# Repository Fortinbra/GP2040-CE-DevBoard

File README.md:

# GP2040-CE-DevBoard
Development board for the GP2040-CE firmware

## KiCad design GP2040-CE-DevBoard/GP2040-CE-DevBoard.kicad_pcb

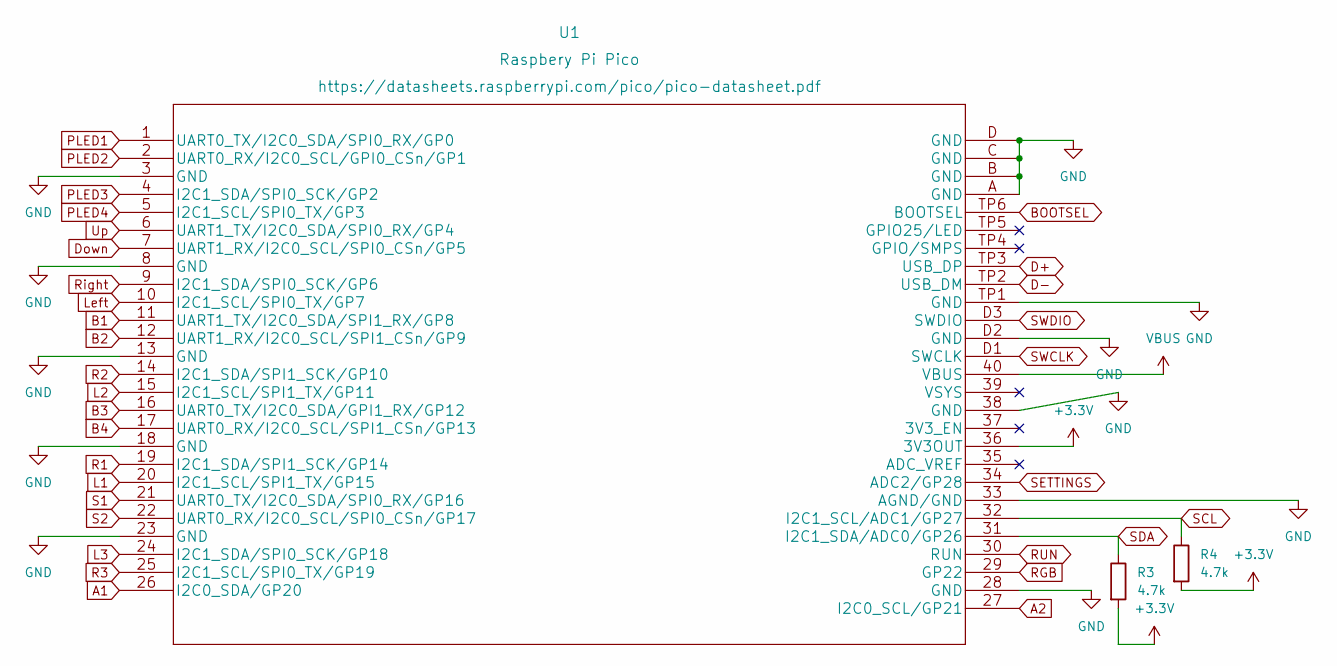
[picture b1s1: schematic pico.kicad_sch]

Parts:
R3, R4: 4.7k; C_0805_2012Metric_Pad1.18x1.45mm_HandSolder
U1: Raspbery Pi Pico; Pico

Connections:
+3V3: R3.2, R4.2, U1.36 (3V3OUT); also elsewhere on the board
A1: U1.26 (I2C0_SDA/GP20); also elsewhere on the board
A2: U1.27 (I2C0_SCL/GP21); also elsewhere on the board
B1: U1.11 (UART1_TX/I2C0_SDA/SPI1_RX/GP8); also elsewhere on the board
B2: U1.12 (UART1_RX/I2C0_SCL/SPI1_CSn/GP9); also elsewhere on the board
B3: U1.16 (UART0_TX/I2C0_SDA/GPI1_RX/GP12); also elsewhere on the board
B4: U1.17 (UART0_RX/I2C0_SCL/SPI1_CSn/GP13); also elsewhere on the board
BOOTSEL: U1.TP6 (BOOTSEL); also elsewhere on the board
D+: U1.TP3 (USB_DP); also elsewhere on the board
D-: U1.TP2 (USB_DM); also elsewhere on the board
Down: U1.7 (UART1_RX/I2C0_SCL/SPI0_CSn/GP5); also elsewhere on the board
GND: U1.3 (GND), U1.8 (GND), U1.13 (GND), U1.18 (GND), U1.23 (GND), U1.28 (GND), U1.33 (AGND/GND), U1.38 (GND), U1.A (GND), U1.B (GND), U1.C (GND), U1.D (GND), U1.D2 (GND), U1.TP1 (GND); also elsewhere on the board
L1: U1.20 (I2C1_SCL/SPI1_TX/GP15); also elsewhere on the board
L2: U1.15 (I2C1_SCL/SPI1_TX/GP11); also elsewhere on the board
L3: U1.24 (I2C1_SDA/SPI0_SCK/GP18); also elsewhere on the board
Left: U1.10 (I2C1_SCL/SPI0_TX/GP7); also elsewhere on the board
PLED1: U1.1 (UART0_TX/I2C0_SDA/SPI0_RX/GP0); also elsewhere on the board
PLED2: U1.2 (UART0_RX/I2C0_SCL/GPI0_CSn/GP1); also elsewhere on the board
PLED3: U1.4 (I2C1_SDA/SPI0_SCK/GP2); also elsewhere on the board
PLED4: U1.5 (I2C1_SCL/SPI0_TX/GP3); also elsewhere on the board
R1: U1.19 (I2C1_SDA/SPI1_SCK/GP14); also elsewhere on the board
R2: U1.14 (I2C1_SDA/SPI1_SCK/GP10); also elsewhere on the board
R3: U1.25 (I2C1_SCL/SPI0_TX/GP19); also elsewhere on the board
RGB: U1.29 (GP22); also elsewhere on the board
RUN: U1.30 (RUN); also elsewhere on the board
Right: U1.9 (I2C1_SDA/SPI0_SCK/GP6); also elsewhere on the board
S1: U1.21 (UART0_TX/I2C0_SDA/SPI0_RX/GP16); also elsewhere on the board
S2: U1.22 (UART0_RX/I2C0_SCL/SPI0_CSn/GP17); also elsewhere on the board
SCL: R4.1, U1.32 (I2C1_SCL/ADC1/GP27); also elsewhere on the board
SDA: R3.1, U1.31 (I2C1_SDA/ADC0/GP26); also elsewhere on the board
SETTINGS: U1.34 (ADC2/GP28); also elsewhere on the board
SWCLK: U1.D1 (SWCLK); also elsewhere on the board
SWDIO: U1.D3 (SWDIO); also elsewhere on the board
Up: U1.6 (UART1_TX/I2C0_SDA/SPI0_RX/GP4); also elsewhere on the board
VBUS: U1.40 (VBUS); also elsewhere on the board

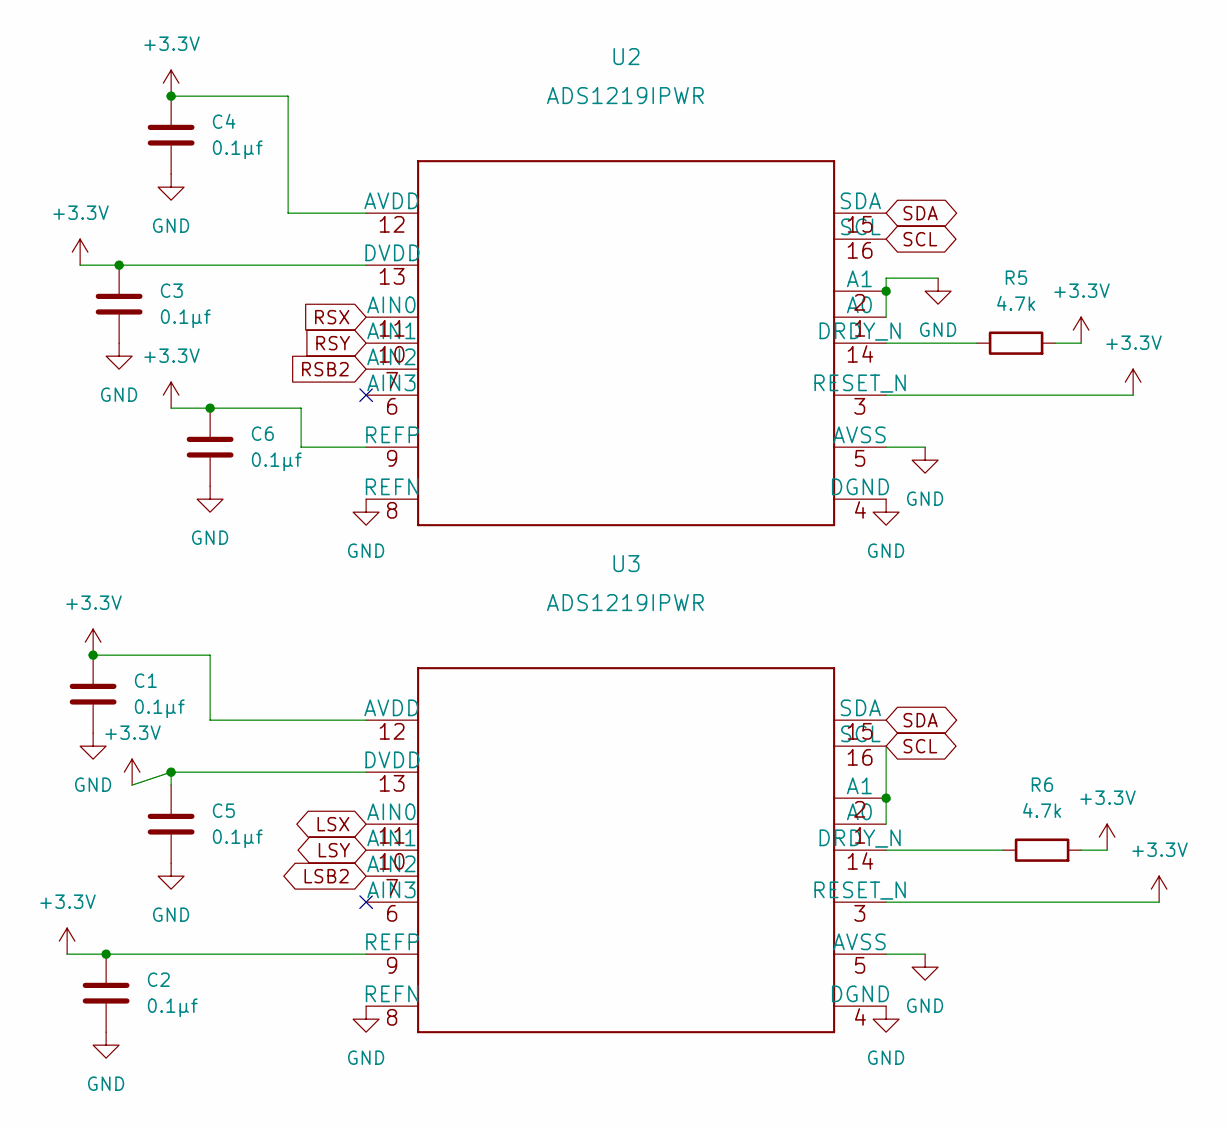
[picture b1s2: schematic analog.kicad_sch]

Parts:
C1, C2, C3, C4, C5, C6: 0.1μf; C_0805_2012Metric_Pad1.18x1.45mm_HandSolder
R5, R6: 4.7k; R_0805_2012Metric_Pad1.20x1.40mm_HandSolder
U2, U3: ADS1219IPWR

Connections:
+3V3: C1.1, C2.1, C3.1, C4.1, C5.1, C6.1, R5.2, R6.2, U2.3 (RESET_N), U2.9 (REFP), U2.12 (AVDD), U2.13 (DVDD), U3.3 (RESET_N), U3.9 (REFP), U3.12 (AVDD), U3.13 (DVDD); also elsewhere on the board
GND: C1.2, C2.2, C3.2, C4.2, C5.2, C6.2, U2.1 (A0), U2.2 (A1), U2.4 (DGND), U2.5 (AVSS), U2.8 (REFN), U3.4 (DGND), U3.5 (AVSS), U3.8 (REFN); also elsewhere on the board
LSB2: U3.7 (AIN2); also elsewhere on the board
LSX: U3.11 (AIN0); also elsewhere on the board
LSY: U3.10 (AIN1); also elsewhere on the board
unnamed: R5.1, U2.14 (DRDY_N)
unnamed: R6.1, U3.14 (DRDY_N)
RSB2: U2.7 (AIN2); also elsewhere on the board
RSX: U2.11 (AIN0); also elsewhere on the board
RSY: U2.10 (AIN1); also elsewhere on the board
SCL: U2.16 (SCL), U3.1 (A0), U3.2 (A1), U3.16 (SCL); also elsewhere on the board
SDA: U2.15 (SDA), U3.15 (SDA); also elsewhere on the board

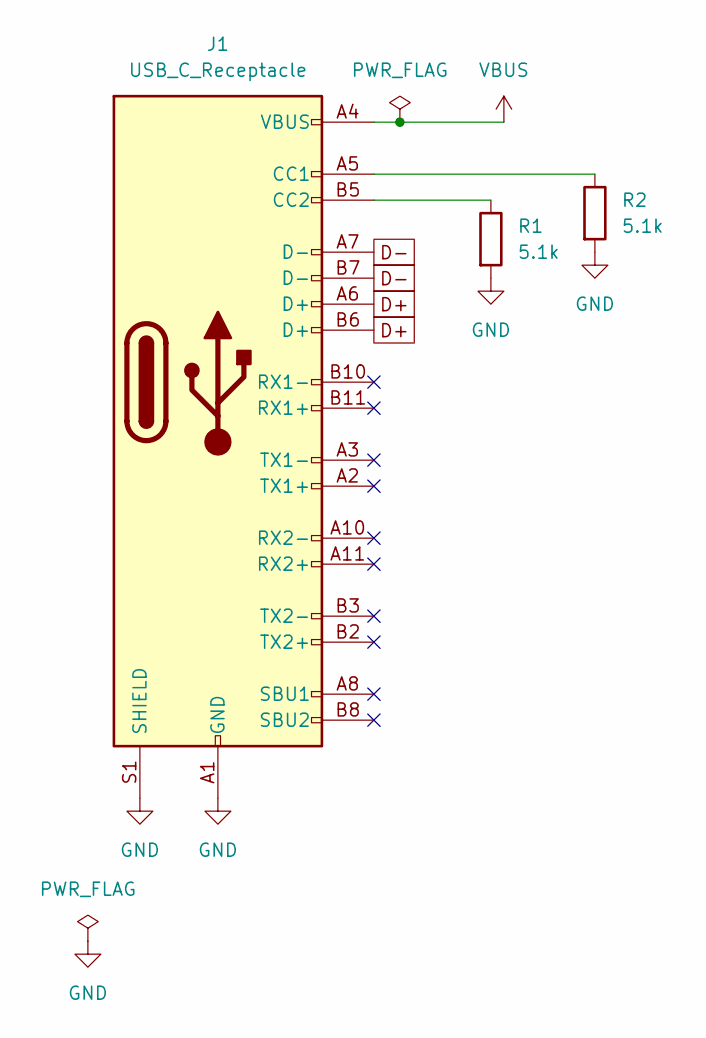
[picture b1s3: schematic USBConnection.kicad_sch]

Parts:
J1: USB_C_Receptacle; USB_C_Receptacle_GCT_USB4085
R1, R2: 5.1k; R_0805_2012Metric_Pad1.20x1.40mm_HandSolder

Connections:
D+: J1.A6 (D+), J1.B6 (D+); also elsewhere on the board
D-: J1.A7 (D-), J1.B7 (D-); also elsewhere on the board
GND: J1.A1 (GND), J1.A12 (GND), J1.B1 (GND), J1.B12 (GND), J1.S1 (SHIELD), R1.2, R2.2; also elsewhere on the board
unnamed: J1.A5 (CC1), R2.1
unnamed: J1.B5 (CC2), R1.1
VBUS: J1.A4 (VBUS), J1.A9 (VBUS), J1.B4 (VBUS), J1.B9 (VBUS); also elsewhere on the board

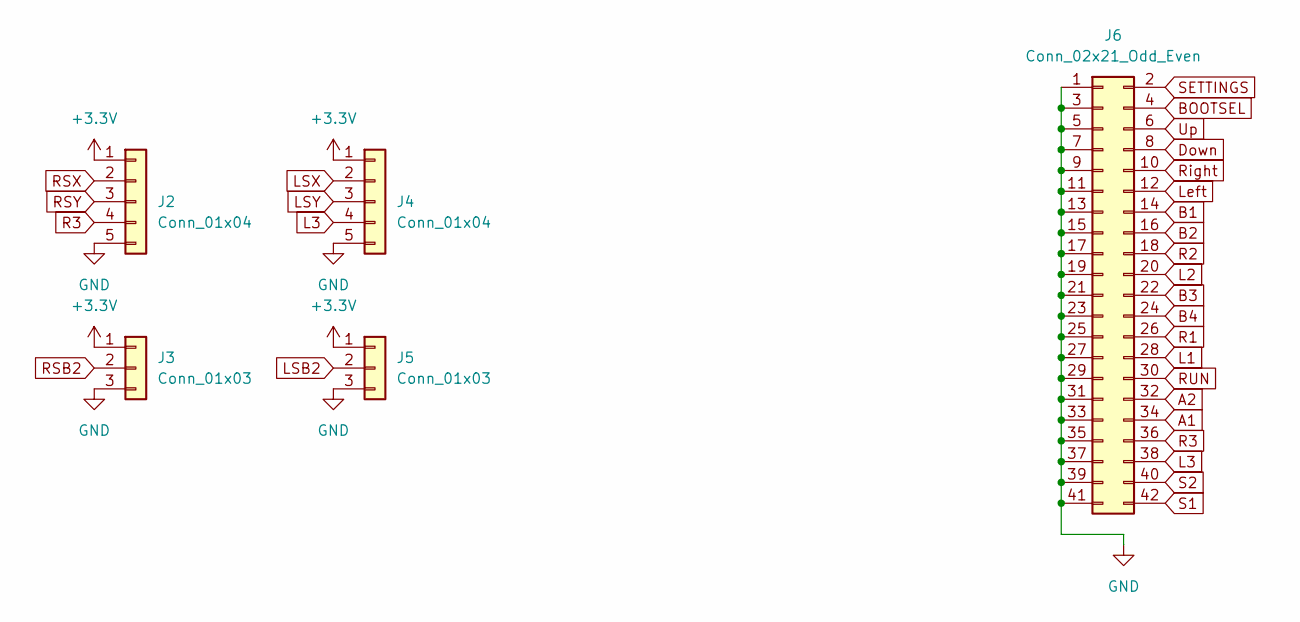
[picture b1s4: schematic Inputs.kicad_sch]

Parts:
J2, J4: Conn_01x04; PinHeader_1x05_P2.54mm_Vertical
J3: Conn_01x03
J5: Conn_01x03; PinHeader_1x03_P2.54mm_Vertical
J6: Conn_02x21_Odd_Even; PinHeader_2x21_P2.54mm_Vertical

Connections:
+3V3: J2.1, J3.1, J4.1, J5.1; also elsewhere on the board
A1: J6.34; also elsewhere on the board
A2: J6.32; also elsewhere on the board
B1: J6.14; also elsewhere on the board
B2: J6.16; also elsewhere on the board
B3: J6.22; also elsewhere on the board
B4: J6.24; also elsewhere on the board
BOOTSEL: J6.4; also elsewhere on the board
Down: J6.8; also elsewhere on the board
GND: J2.5, J3.3, J4.5, J5.3, J6.1, J6.3, J6.5, J6.7, J6.9, J6.11, J6.13, J6.15, J6.17, J6.19, J6.21, J6.23, J6.25, J6.27, J6.29, J6.31, J6.33, J6.35, J6.37, J6.39, J6.41; also elsewhere on the board
L1: J6.28; also elsewhere on the board
L2: J6.20; also elsewhere on the board
L3: J4.4, J6.38; also elsewhere on the board
LSB2: J5.2; also elsewhere on the board
LSX: J4.2; also elsewhere on the board
LSY: J4.3; also elsewhere on the board
Left: J6.12; also elsewhere on the board
R1: J6.26; also elsewhere on the board
R2: J6.18; also elsewhere on the board
R3: J2.4, J6.36; also elsewhere on the board
RSB2: J3.2; also elsewhere on the board
RSX: J2.2; also elsewhere on the board
RSY: J2.3; also elsewhere on the board
RUN: J6.30; also elsewhere on the board
Right: J6.10; also elsewhere on the board
S1: J6.42; also elsewhere on the board
S2: J6.40; also elsewhere on the board
SETTINGS: J6.2; also elsewhere on the board
Up: J6.6; also elsewhere on the board

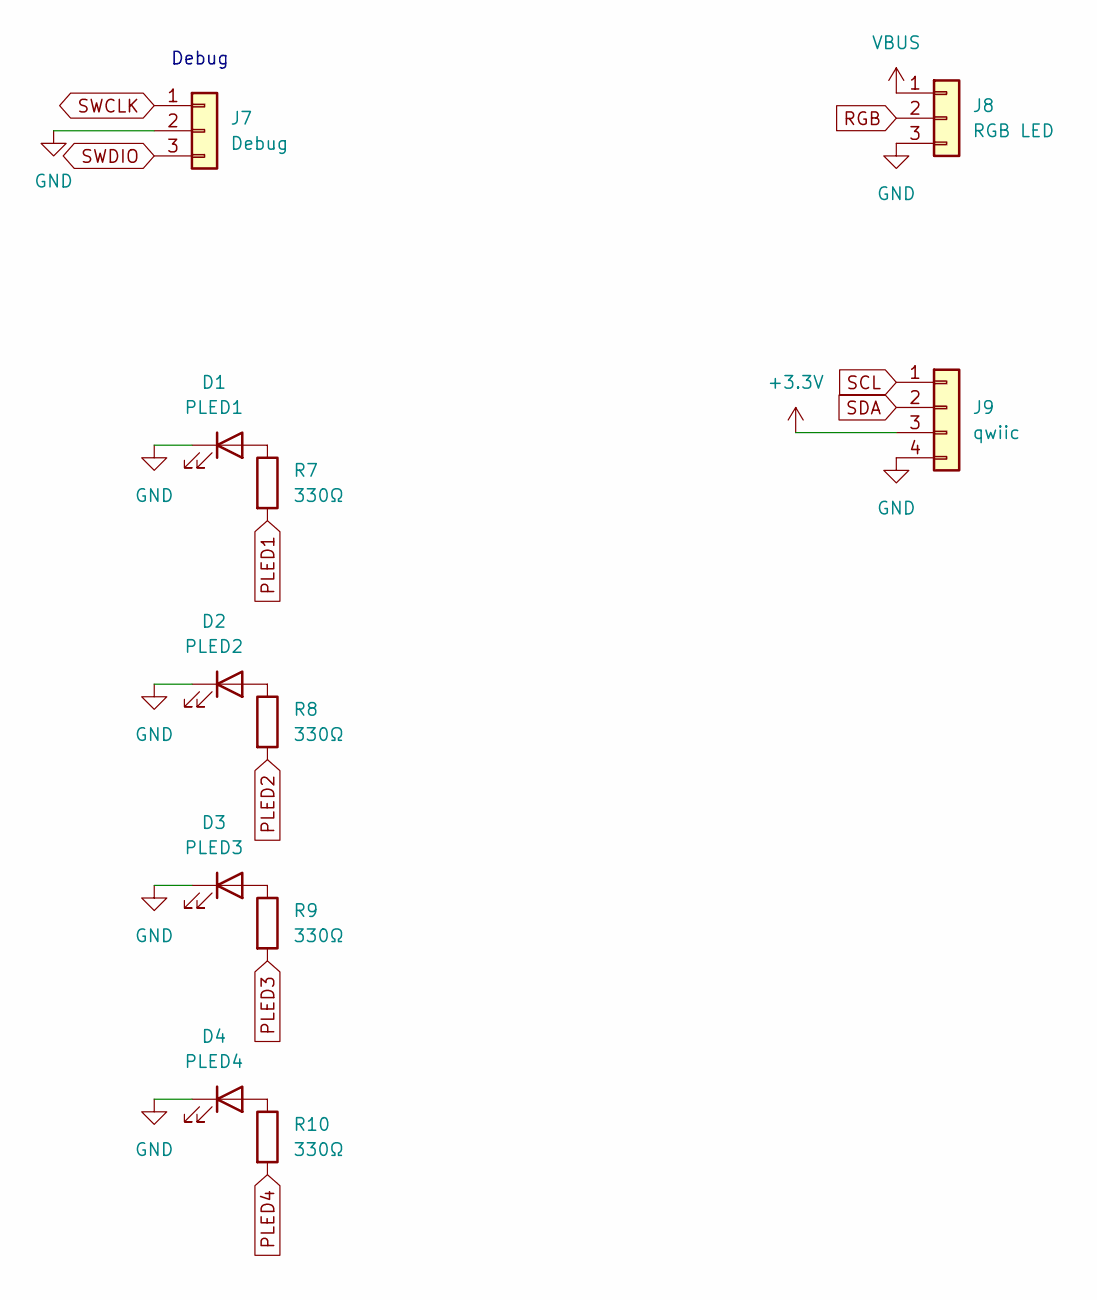
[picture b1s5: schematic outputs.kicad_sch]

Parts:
D1: PLED1; LED_0805_2012Metric_Pad1.15x1.40mm_HandSolder
D2: PLED2; LED_0805_2012Metric_Pad1.15x1.40mm_HandSolder
D3: PLED3; LED_0805_2012Metric_Pad1.15x1.40mm_HandSolder
D4: PLED4; LED_0805_2012Metric_Pad1.15x1.40mm_HandSolder
J7: Debug; PinSocket_1x03_P2.54mm_Vertical
J8: RGB LED; PinSocket_1x03_P2.54mm_Vertical
J9: qwiic; JST_SH_SM04B-SRSS-TB_1x04-1MP_P1.00mm_Horizontal
R7, R8, R9, R10: 330Ω; R_0805_2012Metric_Pad1.20x1.40mm_HandSolder

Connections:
+3V3: J9.3; also elsewhere on the board
GND: D1.1 (K), D2.1 (K), D3.1 (K), D4.1 (K), J7.2, J8.3, J9.4; also elsewhere on the board
unnamed: D1.2 (A), R7.1
unnamed: D2.2 (A), R8.1
unnamed: D3.2 (A), R9.1
unnamed: D4.2 (A), R10.1
PLED1: R7.2; also elsewhere on the board
PLED2: R8.2; also elsewhere on the board
PLED3: R9.2; also elsewhere on the board
PLED4: R10.2; also elsewhere on the board
RGB: J8.2; also elsewhere on the board
SCL: J9.1; also elsewhere on the board
SDA: J9.2; also elsewhere on the board
SWCLK: J7.1; also elsewhere on the board
SWDIO: J7.3; also elsewhere on the board
VBUS: J8.1; also elsewhere on the board

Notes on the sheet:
Debug

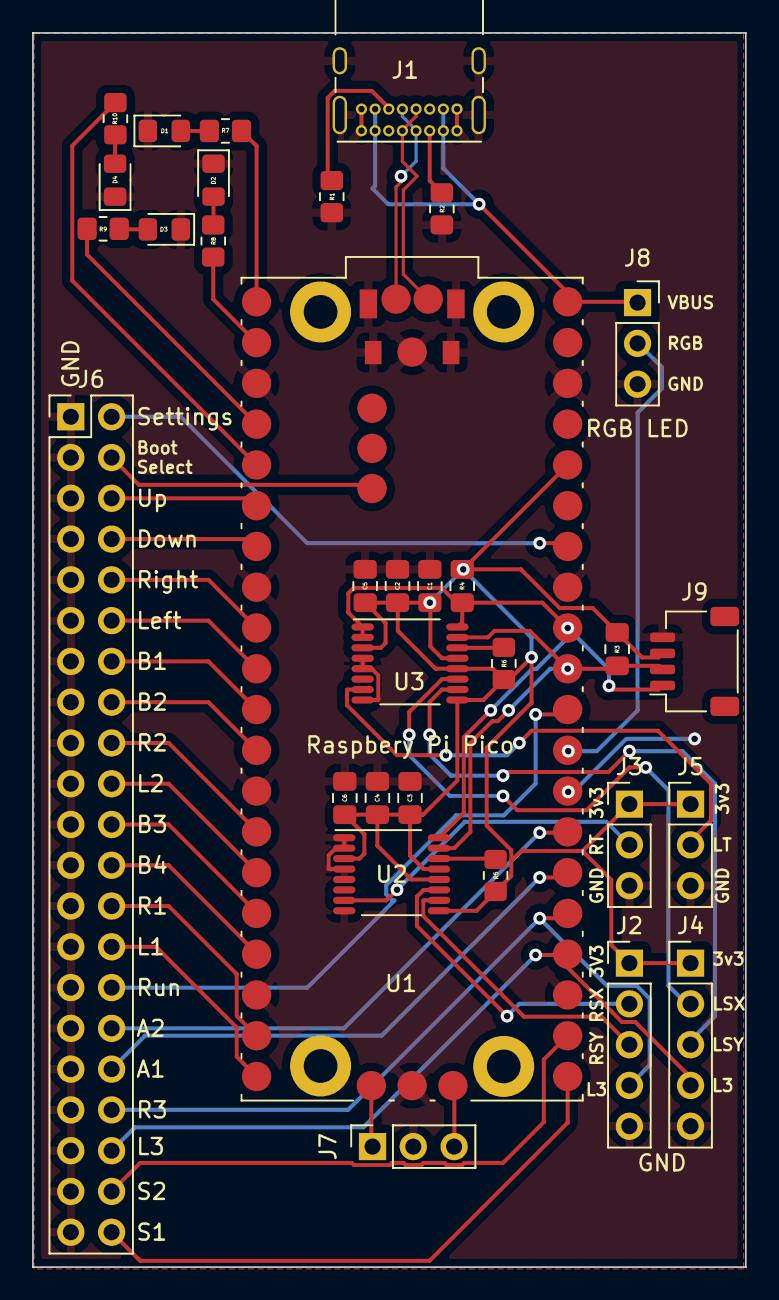
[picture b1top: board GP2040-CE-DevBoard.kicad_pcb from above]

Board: 2 copper layers, 44.4 x 76.9 mm, 32 parts (0 on the bottom side), 49 nets.

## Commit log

2022-05-26 Creating project
2022-05-27 Creating schematic hierarchy
2022-05-27 Adding Buttons
2022-05-27 Schematic nearly complete, PCB started
2022-05-29 Restarting PCB design
2022-06-12 Updating schema and PCB design
2022-06-17 progress
2022-06-17 routing by hand is a pain
2022-06-19 Nearly finished!
2022-06-28 sync
2022-07-10 Cleanup
2022-07-10 a lot of Silkscreen work

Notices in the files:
parts and their libraries:
Copyright 2021 Accelerated Designs. All rights reserved.
